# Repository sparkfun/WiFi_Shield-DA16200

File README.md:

SparkFun WiFi Shield DA16200
========================================

[*SparkFun WiFi Shield DA16200 (18567)*](https://www.sparkfun.com/products/18567)

Ultra. Low. Power. Arguably the best three words in the IoT world. SparkFun has teamed up with Dialog to provide you with this [Ultra-Low_Power Wifi Shield](https://www.sparkfun.com/products/18567) based around the DA16200 module. Behold a fully integrated Wi-Fi® module with a 40 MHz crystal oscillator, 32.768 KHz RTC clock, RF Lumped RF filter, 4 M-byte flash memory, and an onboard chip antenna. Add to that a Qwiic connector, MORE STUFF, and you've got pure magic. 

This module is ideal for door locks, thermostats, sensors, pet trackers, asset trackers, sprinkler systems, connected lighting, video cameras, video door bells, wearables and other IoT devices.

The module's certified Wi-Fi alliance for IEEE802.11b/g/n, Wi-Fi Direct, WPS functionalities means it's been approved by multiple countries and using the Wi-Fi Alliance transfer policy, the Wi-Fi Certifications can be transferred without being tested again. 

Repository Contents
-------------------

* **/Hardware** - Eagle design files (.brd, .sch)

Documentation
--------------
* **[Hookup Guide](https://sparkle.sparkfun.com/sparkle/learn_tutorials/1991)** - Basic hookup guide for the SparkFun WiFi Shield DA16200.

License Information
-------------------

This product is _**open source**_! 

Please review the LICENSE.md file for license information. 

If you have any questions or concerns on licensing, please contact technical support on our [SparkFun forums](https://forum.sparkfun.com/viewforum.php?f=152).

Distributed as-is; no warranty is given.

- Your friends at SparkFun.

_<COLLABORATION CREDIT>_

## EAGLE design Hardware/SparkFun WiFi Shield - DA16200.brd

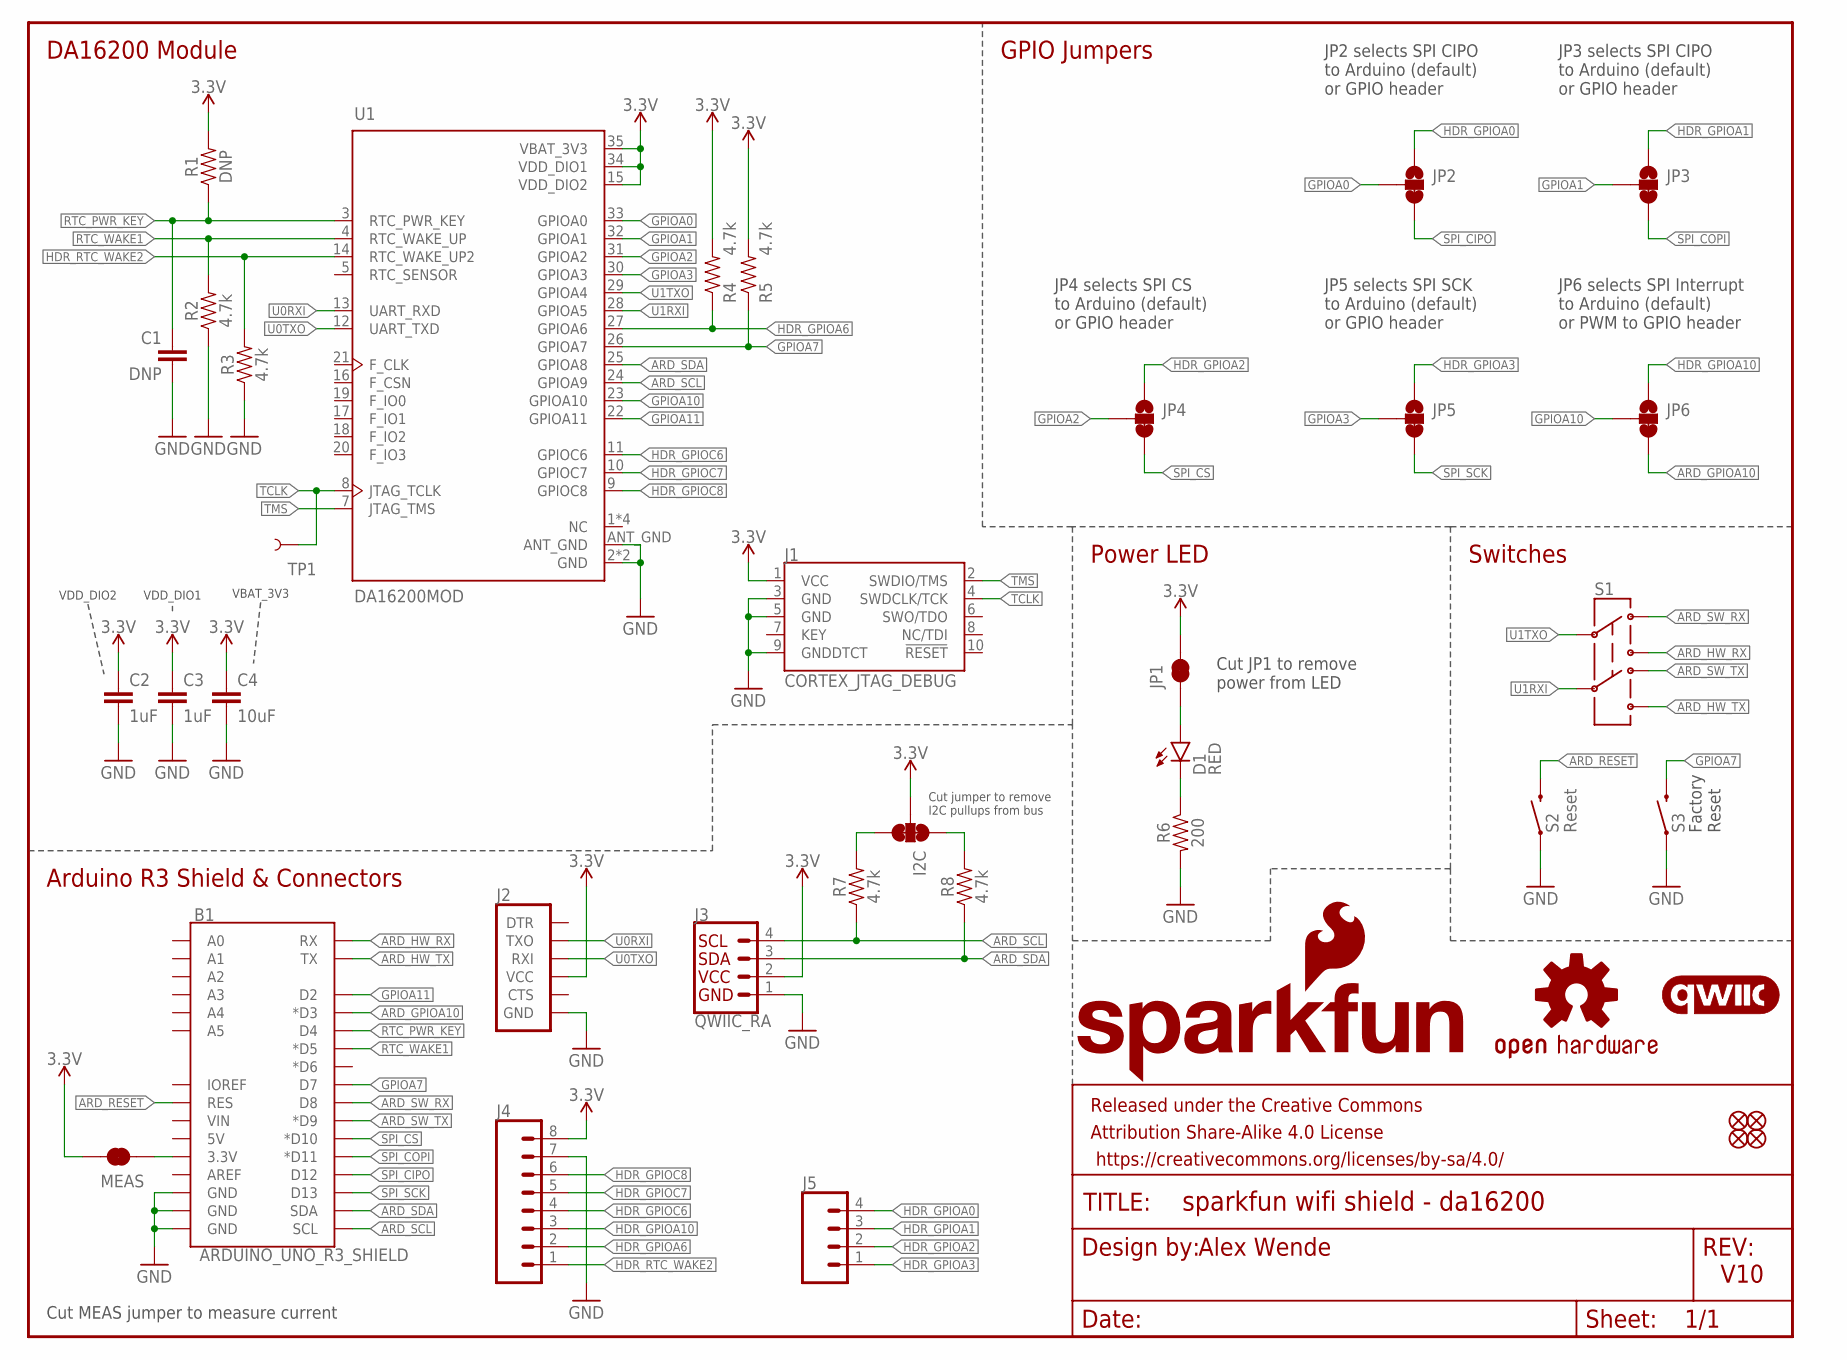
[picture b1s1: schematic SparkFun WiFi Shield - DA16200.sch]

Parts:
B1: ARDUINO_UNO_R3_SHIELD; UNO_R3_SHIELD_NOLABELS_LOCK
C1: DNP; 0603
C2, C3: 1uF; 0603
C4: 10uF; 0603
D1: RED; LED-0603
FD1, FD2, FD3, FD4: FIDUCIAL1X2; FIDUCIAL-1X2
FRAME1: FRAME-LETTER; CREATIVE_COMMONS
I2C: JUMPER-SMT_3_2-NC_TRACE_SILK; SMT-JUMPER_3_2-NC_TRACE_SILK
J1: CORTEX_JTAG_DEBUG; 2X5-PTH-1.27MM-NO_SILK
J2: 6_PIN_SERIAL_TARGET_NO_SILK; 1X06_NO_SILK
J3: QWIIC_RA; JST04_1MM_RA
J4: CONN_08NO_SILK_DNP; 1X08_NO_SILK
J5: CONN_041X04_NO_SILK; 1X04_NO_SILK
JP1: JUMPER-SMT_2_NC_TRACE_SILK; SMT-JUMPER_2_NC_TRACE_SILK
JP2, JP3, JP4, JP5, JP6: JUMPER-SMT_3_1-NC_TRACE_SILK; SMT-JUMPER_3_1-NC_TRACE_SILK
LOGO1: SFE_LOGO_NAME_FLAME.2_INCH; SFE_LOGO_NAME_FLAME_.2
LOGO2: OSHW-LOGOM; OSHW-LOGO-M
LOGO4: QWIIC_LOGO_5MM; QWIIC_5MM
MEAS: JUMPER-COMBO_2_NC_TRACE; COMBO-JUMPER_2_NC_TRACE
R1: DNP; 0603
R2, R3, R4, R5, R7, R8: 4.7k; 0603
R6: 200; 0603
S1: DPDT; SWITCH_DPDT_SMD_AYZ0202
S2: Reset; TACTILE_SWITCH_SMD_5.2MM
S3: MOMENTARY-SWITCH-SPST-SMD-5.2MM-TALL; TACTILE_SWITCH_SMD_5.2MM
TP1: TEST-POINT3; PAD.03X.03
U1: DA16200MOD; XCVR_DA16200MOD-AAC4WA32

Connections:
3.3V: C2.1, C3.1, C4.1, I2C.2, J1.1 (VCC), J2.4 (VCC), J3.2, J4.8, JP1.2, MEAS.1, MEAS.3 (1), R1.2, R4.2, R5.2, U1.15 (VDD_DIO2), U1.34 (VDD_DIO1), U1.35 (VBAT_3V3)
ARD_GPIOA10: B1.D3 (*D3), JP6.3
ARD_HW_RX: B1.RX, S1.1
ARD_HW_TX: B1.TX, S1.4
ARD_RESET: B1.RES, S2.3 (2)
ARD_SCL: B1.SCL, J3.4, R7.1, U1.24 (GPIOA9)
ARD_SDA: B1.SDA, J3.3, R8.1, U1.25 (GPIOA8)
ARD_SW_RX: B1.D8, S1.3
ARD_SW_TX: B1.D9 (*D9), S1.6
GND: B1.GND@0 (GND), B1.GND@1 (GND), B1.GND@2 (GND), C1.2, C2.2, C3.2, C4.2, J1.3 (GND), J1.5 (GND), J1.9 (GNDDTCT), J2.6 (GND), J3.1, J4.7, R2.1, R3.1, R6.2, S2.1, S3.1, U1.2 (GND), U1.ANT_GND, U1.GND
GPIOA0: JP2.2, U1.33 (GPIOA0)
GPIOA1: JP3.2, U1.32 (GPIOA1)
GPIOA2: JP4.2, U1.31 (GPIOA2)
GPIOA3: JP5.2, U1.30 (GPIOA3)
GPIOA7: B1.D7, R5.1, S3.3 (2), U1.26 (GPIOA7)
GPIOA10: JP6.2, U1.23 (GPIOA10)
GPIOA11: B1.D2, U1.22 (GPIOA11)
HDR_GPIOA0: J5.4, JP2.1
HDR_GPIOA1: J5.3, JP3.1
HDR_GPIOA2: J5.2, JP4.1
HDR_GPIOA3: J5.1, JP5.1
HDR_GPIOA6: J4.2, R4.1, U1.27 (GPIOA6)
HDR_GPIOA10: J4.3, JP6.1
HDR_GPIOC6: J4.4, U1.11 (GPIOC6)
HDR_GPIOC7: J4.5, U1.10 (GPIOC7)
HDR_GPIOC8: J4.6, U1.9 (GPIOC8)
HDR_RTC_WAKE2: J4.1, R3.2, U1.14 (RTC_WAKE_UP2)
unnamed: B1.3.3V, MEAS.2, MEAS.4 (2)
unnamed: D1.A, JP1.1
unnamed: I2C.3, R7.2
unnamed: I2C.1, R8.2
unnamed: D1.C, R6.1
RTC_PWR_KEY: B1.D4, C1.1, R1.1, U1.3 (RTC_PWR_KEY)
RTC_WAKE1: B1.D5 (*D5), R2.2, U1.4 (RTC_WAKE_UP)
SPI_CIPO: B1.D12, JP2.3
SPI_COPI: B1.D11 (*D11), JP3.3
SPI_CS: B1.D10 (*D10), JP4.3
SPI_SCK: B1.D13, JP5.3
TCLK: J1.4 (SWDCLK/TCK), TP1.1, U1.8 (JTAG_TCLK)
TMS: J1.2 (SWDIO/TMS), U1.7 (JTAG_TMS)
U0RXI: J2.3 (TXO), U1.13 (UART_RXD)
U0TXO: J2.2 (RXI), U1.12 (UART_TXD)
U1RXI: S1.5, U1.28 (GPIOA5)
U1TXO: S1.2, U1.29 (GPIOA4)

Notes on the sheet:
Factory Reset
DA16200 Module
Arduino R3 Shield & Connectors
Switches
V10
Alex Wende
VDD_DIO2
VDD_DIO1
VBAT_3V3
Power LED
GPIO Jumpers
Cut JP1 to remove power from LED
JP6 selects SPI Interrupt to Arduino (default) or PWM to GPIO header
Cut MEAS jumper to measure current
Cut jumper to remove I2C pullups from bus
JP2 selects SPI CIPO to Arduino (default) or GPIO header
JP3 selects SPI CIPO to Arduino (default) or GPIO header
JP4 selects SPI CS to Arduino (default) or GPIO header
JP5 selects SPI SCK to Arduino (default) or GPIO header

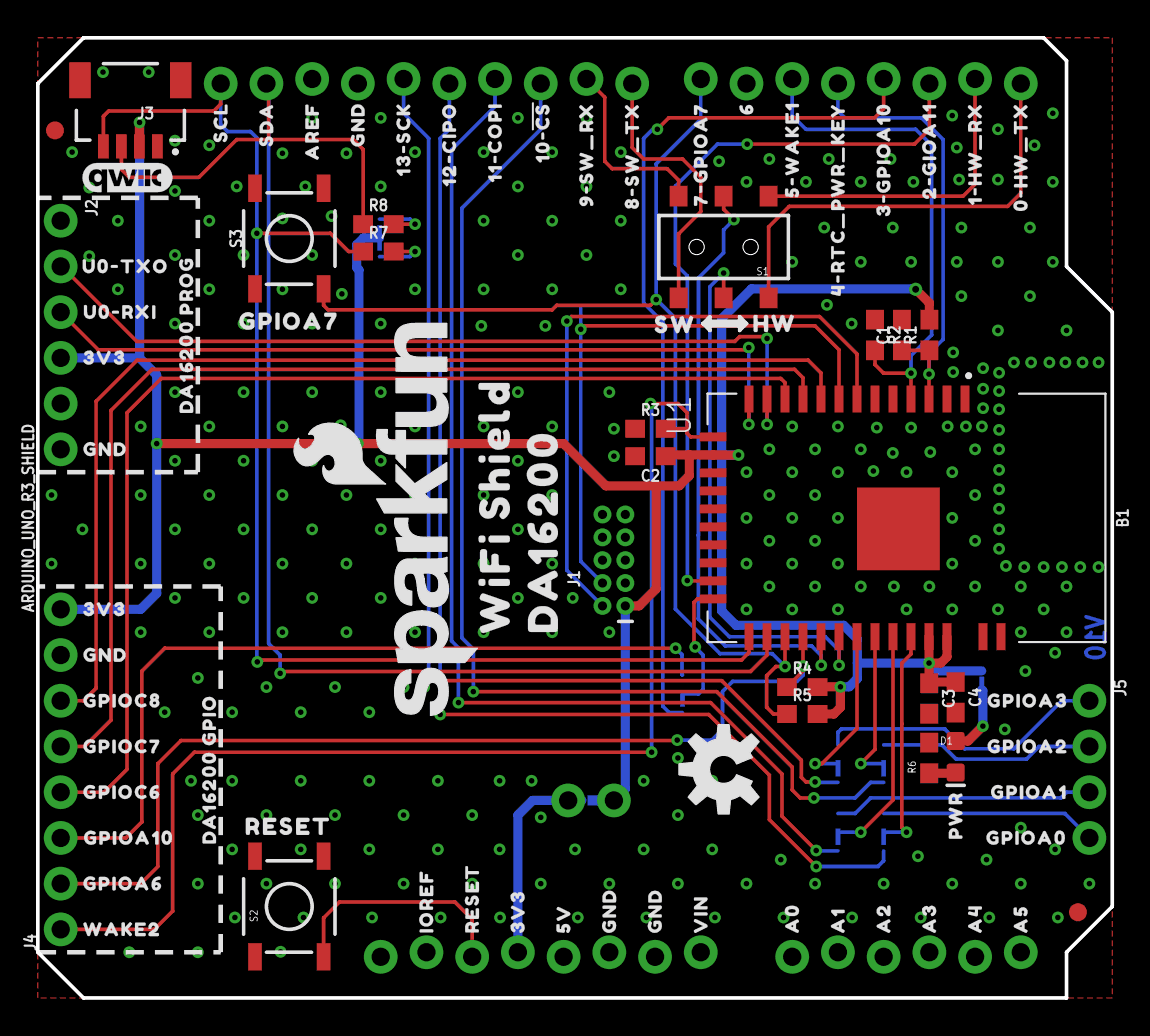
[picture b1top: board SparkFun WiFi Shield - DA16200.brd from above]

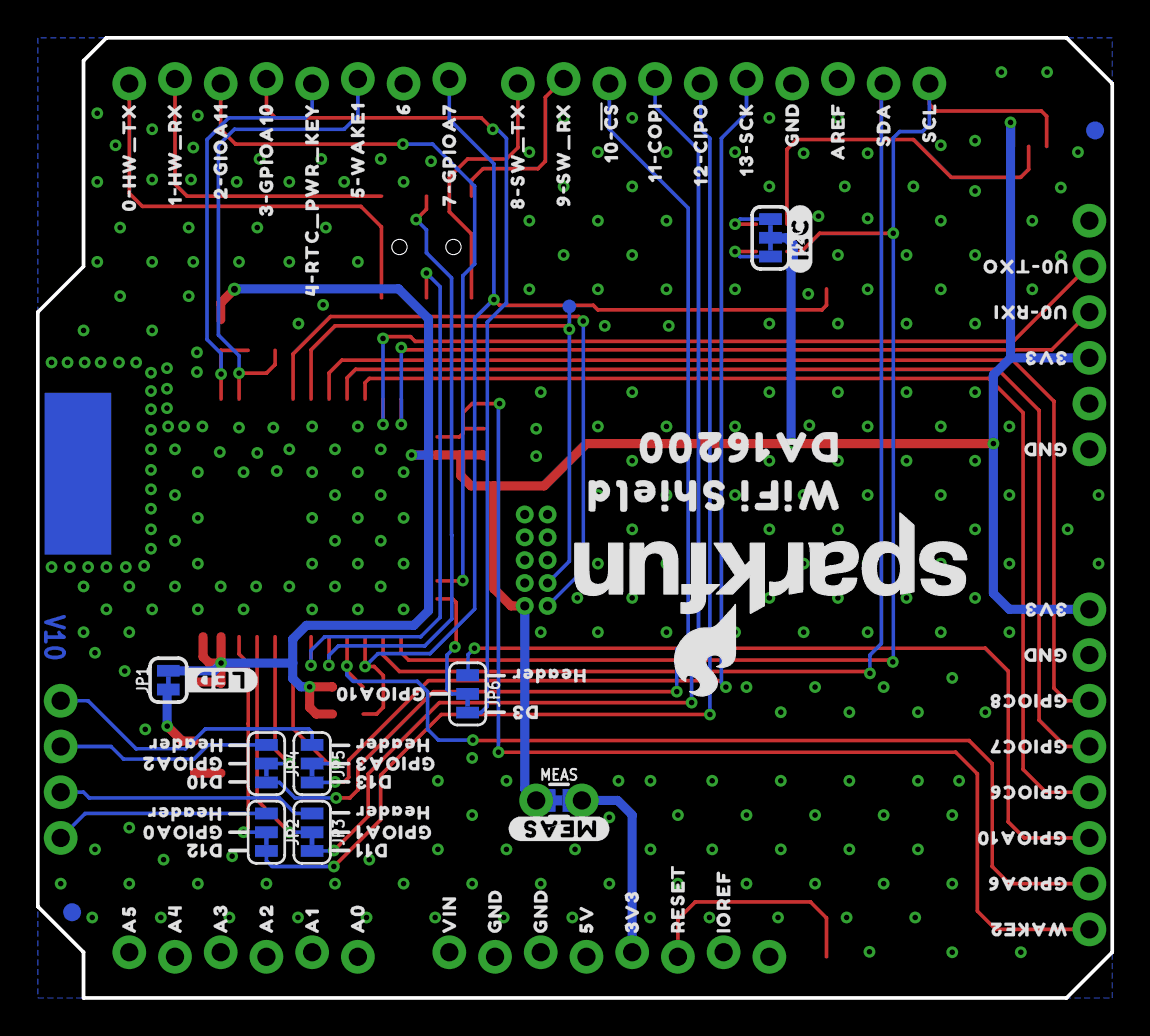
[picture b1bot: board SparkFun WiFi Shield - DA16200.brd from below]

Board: 2 copper layers, 59.7 x 53.3 mm, 160 parts (75 on the bottom side), 44 nets.

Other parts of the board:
LOGO3: SFE_LOGO_NAME_FLAME.2_INCH; SFE_LOGO_NAME_FLAME_.2
U$1, U$16: IOREF0
U$2, U$19: RESET0
U$3, U$37, U$39, U$41, U$85, U$87: 3V30
U$4, U$55: 5V0
U$5, U$6, U$28, U$40, U$52, U$56, U$57, U$79, U$86, U$88: GND0
U$7, U$58: VIN0
U$8, U$59: A00
U$9, U$60: A10
U$10, U$61: A20
U$11, U$62: A30
U$12, U$63: A40
U$13, U$64: A50
U$14, U$65: 0#HW_TX0
U$15, U$66: 1#HW_RX0
U$17, U$95: GPIOA60
U$18, U$70: 4#RTC_PWR_KEY0
U$20, U$73: 8#SW_TX0
U$21, U$72: 7#GPIOA70
U$22, U$67: 2#GIOA110
U$23, U$33: 5#WAKE10
U$24, U$75: 10##CS#0
U$25, U$76: 11#COPI0
U$26, U$77: 12#CIPO0
U$27, U$78: 13#SCK0
U$29, U$80: AREF0
U$30, U$81: SDA0
U$31, U$82: SCL0
U$32, U$74: 9#SW_RX0
U$34: GPIOA70
U$35, U$48: WAKE20
U$36: RESET_0
U$38, U$71: 60
U$42: HW0
U$43: SW0
U$44, U$89: GPIOC80
U$45, U$90: GPIOC70
U$46, U$91: GPIOC60
U$47, U$69, U$92: GPIOA100
U$49: #I2C#0
U$51, U$68: 3#GPIOA100
U$53, U$83: U0#TXO0
U$54, U$84: U0#RXI0
U$93, U$115: GPIOA00
U$94, U$114: GPIOA10
U$96: D30
U$97: #LED#0
U$98: #MEAS#0
U$99: PWR0
U$100, U$107: WIFI_SHIELD0
U$101, U$108: DA162000
U$102, U$116: GPIOA20
U$103, U$117: GPIOA30
U$104: DA16200_GPIO0
U$105: DA16200_PROG0
U$106, U$118, U$119, U$120, U$121: HEADER0
U$122: D100
U$123: D110
U$124: D120
U$125: D130

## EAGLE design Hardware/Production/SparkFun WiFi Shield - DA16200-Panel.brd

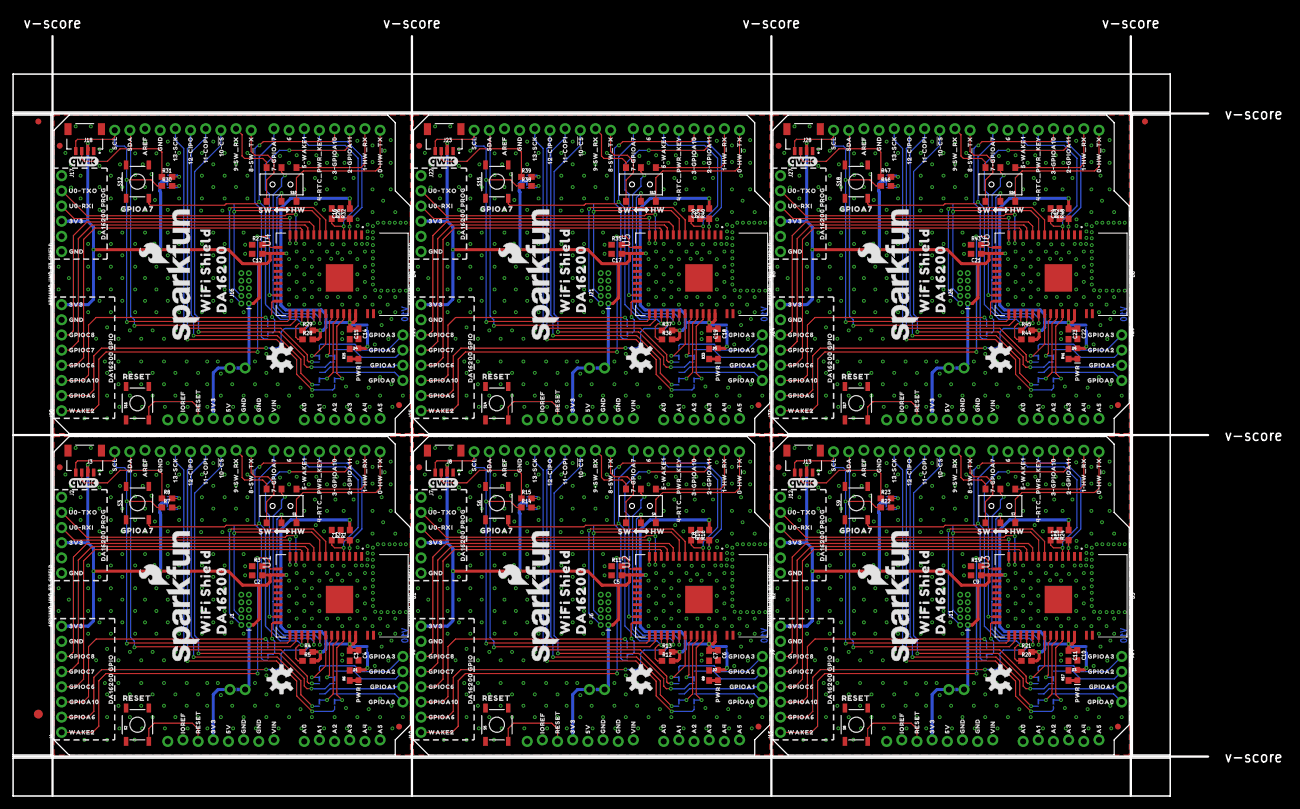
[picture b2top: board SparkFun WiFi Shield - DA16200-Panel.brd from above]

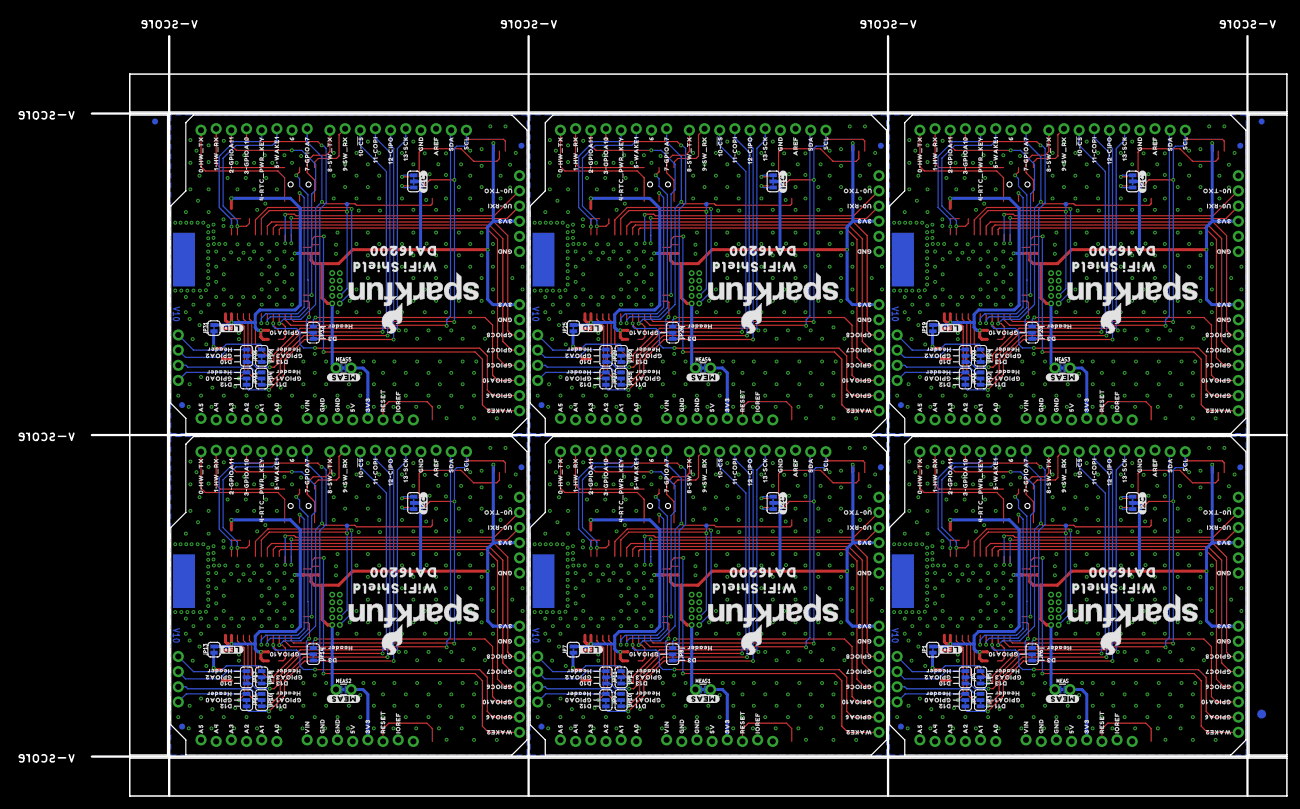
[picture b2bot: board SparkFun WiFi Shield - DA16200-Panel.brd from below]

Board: 2 copper layers, 200.2 x 127.3 mm, 960 parts (453 on the bottom side), 264 nets.

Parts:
B1, B2, B3, B4, B5, B6: ARDUINO_UNO_R3_SHIELD; UNO_R3_SHIELD_NOLABELS_LOCK
C1, C8, C12, C16, C20, C24: DNP; 0603
C2, C3, C5, C7, C9, C11, C13, C15, C17, C19, C21, C23: 1uF; 0603
C4, C6, C10, C14, C18, C22: 10uF; 0603
D1, D2, D3, D4, D5, D6: RED; LED-0603
E$1, E$2, E$3, E$4: FIDUCIAL-1X2
E$5, E$6: FIDUCIAL-1.5X3
FD1, FD2, FD3, FD4, FD5, FD6, FD7, FD8, FD9, FD10, FD11, FD12, FD13, FD14, FD15, FD16, FD17, FD18, FD19, FD20, FD21, FD22, FD23, FD24: FIDUCIAL1X2; FIDUCIAL-1X2
I2C, I2C1, I2C2, I2C3, I2C4, I2C5: SMT-JUMPER_3_2-NC_TRACE_SILK
J1, J6, J11, J16, J21, J26: CORTEX_JTAG_DEBUG; 2X5-PTH-1.27MM-NO_SILK
J2, J7, J12, J17, J22, J27: 1X06_NO_SILK
J3, J8, J13, J18, J23, J28: QWIIC_RA; JST04_1MM_RA
J4, J10, J15, J20, J25, J30: 1X08_NO_SILK
J5, J9, J14, J19, J24, J29: 1X04_NO_SILK
JP1, JP7, JP13, JP19, JP25, JP31: SMT-JUMPER_2_NC_TRACE_SILK
JP2, JP3, JP4, JP5, JP6, JP8, JP9, JP10, JP11, JP12, JP14, JP15, JP16, JP17, JP18, JP20, JP21, JP22, JP23, JP24, JP26, JP27, JP28, JP29, JP30, JP32, JP33, JP34, JP35, JP36: SMT-JUMPER_3_1-NC_TRACE_SILK
LOGO1, LOGO3, LOGO5, LOGO7, LOGO9, LOGO11, LOGO13, LOGO15, LOGO17, LOGO19, LOGO21, LOGO23: SFE_LOGO_NAME_FLAME.2_INCH; SFE_LOGO_NAME_FLAME_.2
LOGO2, LOGO6, LOGO10, LOGO14, LOGO18, LOGO22: OSHW-LOGOM; OSHW-LOGO-M
LOGO4, LOGO8, LOGO12, LOGO16, LOGO20, LOGO24: QWIIC_LOGO_5MM; QWIIC_5MM
MEAS, MEAS1, MEAS2, MEAS3, MEAS4, MEAS5: COMBO-JUMPER_2_NC_TRACE
R1, R16, R24, R32, R40, R48: DNP; 0603
R2, R3, R4, R5, R7, R8, R10, R11, R12, R13, R14, R15, R18, R19, R20, R21, R22, R23, R26, R27, R28, R29, R30, R31, R34, R35, R36, R37, R38, R39, R42, R43, R44, R45, R46, R47: 4.7k; 0603
R6, R9, R17, R25, R33, R41: 200; 0603
S1, S4, S7, S10, S13, S16: DPDT; SWITCH_DPDT_SMD_AYZ0202
S2, S5, S8, S11, S14, S17: Reset; TACTILE_SWITCH_SMD_5.2MM
S3, S6, S9, S12, S15, S18: TACTILE_SWITCH_SMD_5.2MM
TP1, TP2, TP3, TP4, TP5, TP6: PAD.03X.03
U1, U2, U3, U4, U5, U6: DA16200MOD; XCVR_DA16200MOD-AAC4WA32
U$1, U$16, U$22, U$162, U$239, U$281, U$358, U$400, U$477, U$519, U$596, U$638: IOREF0
U$2, U$19, U$67, U$163, U$240, U$282, U$359, U$401, U$478, U$520, U$597, U$639: RESET0
U$3, U$37, U$39, U$41, U$85, U$87, U$110, U$152, U$155, U$164, U$191, U$193, U$241, U$271, U$274, U$283, U$310, U$312, U$360, U$390, U$393, U$402, U$429, U$431, U$479, U$509, U$512, U$521, U$548, U$550, U$598, U$628, U$631, U$640, U$667, U$669: 3V30
U$4, U$55, U$111, U$165, U$242, U$284, U$361, U$403, U$480, U$522, U$599, U$641: 5V0
U$5, U$6, U$28, U$40, U$52, U$56, U$57, U$79, U$86, U$88, U$112, U$113, U$140, U$153, U$154, U$166, U$167, U$185, U$192, U$194, U$243, U$244, U$259, U$272, U$273, U$285, U$286, U$304, U$311, U$313, U$362, U$363, U$378, U$391, U$392, U$404, U$405, U$423, U$430, U$432, U$481, U$482, U$497, U$510, U$511, U$523, U$524, U$542, U$549, U$551, U$600, U$601, U$616, U$629, U$630, U$642, U$643, U$661, U$668, U$670: GND0
U$7, U$58, U$126, U$168, U$245, U$287, U$364, U$406, U$483, U$525, U$602, U$644: VIN0
U$8, U$59, U$127, U$169, U$246, U$288, U$365, U$407, U$484, U$526, U$603, U$645: A00
U$9, U$60, U$128, U$170, U$247, U$289, U$366, U$408, U$485, U$527, U$604, U$646: A10
U$10, U$61, U$129, U$171, U$248, U$290, U$367, U$409, U$486, U$528, U$605, U$647: A20
U$11, U$62, U$130, U$172, U$249, U$291, U$368, U$410, U$487, U$529, U$606, U$648: A30
U$12, U$63, U$131, U$173, U$250, U$292, U$369, U$411, U$488, U$530, U$607, U$649: A40
U$13, U$64, U$132, U$174, U$251, U$293, U$370, U$412, U$489, U$531, U$608, U$650: A50
U$14, U$65, U$133, U$175, U$252, U$294, U$371, U$413, U$490, U$532, U$609, U$651: 0#HW_TX0
U$15, U$66, U$134, U$176, U$253, U$295, U$372, U$414, U$491, U$533, U$610, U$652: 1#HW_RX0
U$17, U$95, U$158, U$199, U$277, U$318, U$396, U$437, U$515, U$556, U$634, U$675: GPIOA60
U$18, U$70, U$231, U$234, U$350, U$353, U$469, U$472, U$588, U$591, U$707, U$710: 4#RTC_PWR_KEY0
U$20, U$73, U$159, U$179, U$278, U$298, U$397, U$417, U$516, U$536, U$635, U$655: 8#SW_TX0
U$21, U$72, U$135, U$178, U$254, U$297, U$373, U$416, U$492, U$535, U$611, U$654: 7#GPIOA70
U$23, U$33, U$232, U$233, U$351, U$352, U$470, U$471, U$589, U$590, U$708, U$709: 5#WAKE10
U$24, U$75, U$136, U$181, U$255, U$300, U$374, U$419, U$493, U$538, U$612, U$657: 10##CS#0
U$25, U$76, U$137, U$182, U$256, U$301, U$375, U$420, U$494, U$539, U$613, U$658: 11#COPI0
U$26, U$77, U$138, U$183, U$257, U$302, U$376, U$421, U$495, U$540, U$614, U$659: 12#CIPO0
U$27, U$78, U$139, U$184, U$258, U$303, U$377, U$422, U$496, U$541, U$615, U$660: 13#SCK0
U$29, U$80, U$141, U$186, U$260, U$305, U$379, U$424, U$498, U$543, U$617, U$662: AREF0
U$30, U$81, U$142, U$187, U$261, U$306, U$380, U$425, U$499, U$544, U$618, U$663: SDA0
U$31, U$82, U$143, U$188, U$262, U$307, U$381, U$426, U$500, U$545, U$619, U$664: SCL0
U$32, U$74, U$160, U$180, U$279, U$299, U$398, U$418, U$517, U$537, U$636, U$656: 9#SW_RX0
U$34, U$144, U$263, U$382, U$501, U$620: GPIOA70
U$35, U$48, U$235, U$236, U$354, U$355, U$473, U$474, U$592, U$593, U$711, U$712: WAKE20
U$36, U$151, U$270, U$389, U$508, U$627: RESET_0
U$38, U$71, U$161, U$177, U$280, U$296, U$399, U$415, U$518, U$534, U$637, U$653: 60
U$42, U$156, U$275, U$394, U$513, U$632: HW0
U$43, U$157, U$276, U$395, U$514, U$633: SW0
U$44, U$89, U$145, U$195, U$264, U$314, U$383, U$433, U$502, U$552, U$621, U$671: GPIOC80
U$45, U$90, U$146, U$196, U$265, U$315, U$384, U$434, U$503, U$553, U$622, U$672: GPIOC70
U$46, U$91, U$147, U$197, U$266, U$316, U$385, U$435, U$504, U$554, U$623, U$673: GPIOC60
U$47, U$69, U$92, U$148, U$198, U$207, U$267, U$317, U$326, U$386, U$436, U$445, U$505, U$555, U$564, U$624, U$674, U$683: GPIOA100
U$49, U$214, U$333, U$452, U$571, U$690: #I2C#0
U$50, U$109, U$237, U$238, U$356, U$357, U$475, U$476, U$594, U$595, U$713, U$714: 2#GPIOA110
U$51, U$68, U$205, U$206, U$324, U$325, U$443, U$444, U$562, U$563, U$681, U$682: 3#GPIOA100
U$53, U$83, U$149, U$189, U$268, U$308, U$387, U$427, U$506, U$546, U$625, U$665: U0#TXO0
U$54, U$84, U$150, U$190, U$269, U$309, U$388, U$428, U$507, U$547, U$626, U$666: U0#RXI0
U$93, U$115, U$216, U$227, U$335, U$346, U$454, U$465, U$573, U$584, U$692, U$703: GPIOA00
U$94, U$114, U$215, U$228, U$334, U$347, U$453, U$466, U$572, U$585, U$691, U$704: GPIOA10
U$96, U$208, U$327, U$446, U$565, U$684: D30
U$97, U$200, U$319, U$438, U$557, U$676: #LED#0
U$98, U$201, U$320, U$439, U$558, U$677: #MEAS#0
U$99, U$202, U$321, U$440, U$559, U$678: PWR0
U$100, U$107, U$210, U$212, U$329, U$331, U$448, U$450, U$567, U$569, U$686, U$688: WIFI_SHIELD0
U$101, U$108, U$211, U$213, U$330, U$332, U$449, U$451, U$568, U$570, U$687, U$689: DA162000
U$102, U$116, U$217, U$229, U$336, U$348, U$455, U$467, U$574, U$586, U$693, U$705: GPIOA20
U$103, U$117, U$218, U$230, U$337, U$349, U$456, U$468, U$575, U$587, U$694, U$706: GPIOA30
U$104, U$203, U$322, U$441, U$560, U$679: DA16200_GPIO0
U$105, U$204, U$323, U$442, U$561, U$680: DA16200_PROG0
U$106, U$118, U$119, U$120, U$121, U$209, U$219, U$220, U$221, U$222, U$328, U$338, U$339, U$340, U$341, U$447, U$457, U$458, U$459, U$460, U$566, U$576, U$577, U$578, U$579, U$685, U$695, U$696, U$697, U$698: HEADER0
U$122, U$223, U$342, U$461, U$580, U$699: D100
U$123, U$224, U$343, U$462, U$581, U$700: D110
U$124, U$225, U$344, U$463, U$582, U$701: D120
U$125, U$226, U$345, U$464, U$583, U$702: D130

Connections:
3.3V: C2.1, C3.1, C4.1, I2C.2, J1.1, J2.4, J3.2, J4.8, JP1.2, MEAS.1, MEAS.3, R1.2, R4.2, R5.2, U1.15, U1.34, U1.35
3.3V1: C5.1, C6.1, C7.1, I2C1.2, J6.1, J7.4, J8.2, J10.8, JP7.2, MEAS1.1, MEAS1.3, R12.2, R13.2, R16.2, U2.15, U2.34, U2.35
3.3V2: C9.1, C10.1, C11.1, I2C2.2, J11.1, J12.4, J13.2, J15.8, JP13.2, MEAS2.1, MEAS2.3, R20.2, R21.2, R24.2, U3.15, U3.34, U3.35
3.3V3: C13.1, C14.1, C15.1, I2C3.2, J16.1, J17.4, J18.2, J20.8, JP19.2, MEAS3.1, MEAS3.3, R28.2, R29.2, R32.2, U4.15, U4.34, U4.35
3.3V4: C17.1, C18.1, C19.1, I2C4.2, J21.1, J22.4, J23.2, J25.8, JP25.2, MEAS4.1, MEAS4.3, R36.2, R37.2, R40.2, U5.15, U5.34, U5.35
3.3V5: C21.1, C22.1, C23.1, I2C5.2, J26.1, J27.4, J28.2, J30.8, JP31.2, MEAS5.1, MEAS5.3, R44.2, R45.2, R48.2, U6.15, U6.34, U6.35
ARD_GPIOA1: B2.D3, JP8.3
ARD_GPIOA2: B3.D3, JP14.3
ARD_GPIOA3: B4.D3, JP20.3
ARD_GPIOA4: B5.D3, JP26.3
ARD_GPIOA5: B6.D3, JP32.3
ARD_GPIOA10: B1.D3, JP6.3
ARD_HW_RX: B1.RX, S1.1
ARD_HW_RX1: B2.RX, S4.1
ARD_HW_RX2: B3.RX, S7.1
ARD_HW_RX3: B4.RX, S10.1
ARD_HW_RX4: B5.RX, S13.1
ARD_HW_RX5: B6.RX, S16.1
ARD_HW_TX: B1.TX, S1.4
ARD_HW_TX1: B2.TX, S4.4
ARD_HW_TX2: B3.TX, S7.4
ARD_HW_TX3: B4.TX, S10.4
ARD_HW_TX4: B5.TX, S13.4
ARD_HW_TX5: B6.TX, S16.4
ARD_RESET: B1.RES, S2.3
ARD_RESET1: B2.RES, S5.3
ARD_RESET2: B3.RES, S8.3
ARD_RESET3: B4.RES, S11.3
ARD_RESET4: B5.RES, S14.3
ARD_RESET5: B6.RES, S17.3
ARD_SCL: B1.SCL, J3.4, R7.1, U1.24
ARD_SCL1: B2.SCL, J8.4, R14.1, U2.24
ARD_SCL2: B3.SCL, J13.4, R22.1, U3.24
ARD_SCL3: B4.SCL, J18.4, R30.1, U4.24
ARD_SCL4: B5.SCL, J23.4, R38.1, U5.24
ARD_SCL5: B6.SCL, J28.4, R46.1, U6.24
ARD_SDA: B1.SDA, J3.3, R8.1, U1.25
ARD_SDA1: B2.SDA, J8.3, R15.1, U2.25
ARD_SDA2: B3.SDA, J13.3, R23.1, U3.25
ARD_SDA3: B4.SDA, J18.3, R31.1, U4.25
ARD_SDA4: B5.SDA, J23.3, R39.1, U5.25
ARD_SDA5: B6.SDA, J28.3, R47.1, U6.25
ARD_SW_RX: B1.D8, S1.3
ARD_SW_RX1: B2.D8, S4.3
ARD_SW_RX2: B3.D8, S7.3
ARD_SW_RX3: B4.D8, S10.3
ARD_SW_RX4: B5.D8, S13.3
ARD_SW_RX5: B6.D8, S16.3
ARD_SW_TX: B1.D9, S1.6
ARD_SW_TX1: B2.D9, S4.6
ARD_SW_TX2: B3.D9, S7.6
ARD_SW_TX3: B4.D9, S10.6
ARD_SW_TX4: B5.D9, S13.6
ARD_SW_TX5: B6.D9, S16.6
GND: B1.GND@0, B1.GND@1, B1.GND@2, C1.2, C2.2, C3.2, C4.2, J1.3, J1.5, J1.9, J2.6, J3.1, J4.7, R2.1, R3.1, R6.2, S2.1, S3.1, U1.2, U1.ANT_GND, U1.GND
GND1: B2.GND@0, B2.GND@1, B2.GND@2, C5.2, C6.2, C7.2, C8.2, J6.3, J6.5, J6.9, J7.6, J8.1, J10.7, R9.2, R10.1, R11.1, S5.1, S6.1, U2.2, U2.ANT_GND, U2.GND
GND2: B3.GND@0, B3.GND@1, B3.GND@2, C9.2, C10.2, C11.2, C12.2, J11.3, J11.5, J11.9, J12.6, J13.1, J15.7, R17.2, R18.1, R19.1, S8.1, S9.1, U3.2, U3.ANT_GND, U3.GND
GND3: B4.GND@0, B4.GND@1, B4.GND@2, C13.2, C14.2, C15.2, C16.2, J16.3, J16.5, J16.9, J17.6, J18.1, J20.7, R25.2, R26.1, R27.1, S11.1, S12.1, U4.2, U4.ANT_GND, U4.GND
GND4: B5.GND@0, B5.GND@1, B5.GND@2, C17.2, C18.2, C19.2, C20.2, J21.3, J21.5, J21.9, J22.6, J23.1, J25.7, R33.2, R34.1, R35.1, S14.1, S15.1, U5.2, U5.ANT_GND, U5.GND
GND5: B6.GND@0, B6.GND@1, B6.GND@2, C21.2, C22.2, C23.2, C24.2, J26.3, J26.5, J26.9, J27.6, J28.1, J30.7, R41.2, R42.1, R43.1, S17.1, S18.1, U6.2, U6.ANT_GND, U6.GND
GPIOA0: JP2.2, U1.33
GPIOA1: JP3.2, U1.32
GPIOA2: JP4.2, U1.31
GPIOA3: JP5.2, U1.30
GPIOA4: B2.D7, R12.1, S6.3, U2.26
GPIOA5: JP8.2, U2.23
GPIOA6: B2.D2, U2.22
GPIOA7: B1.D7, R5.1, S3.3, U1.26
GPIOA8: JP9.2, U2.33
GPIOA9: JP10.2, U2.32
GPIOA10: JP6.2, U1.23
GPIOA11: B1.D2, U1.22
GPIOA12: JP11.2, U2.31
GPIOA13: JP12.2, U2.30
GPIOA14: B3.D7, R20.1, S9.3, U3.26
GPIOA15: JP14.2, U3.23
GPIOA16: B3.D2, U3.22
GPIOA17: JP15.2, U3.33
GPIOA18: JP16.2, U3.32
GPIOA19: JP17.2, U3.31
GPIOA20: JP18.2, U3.30
GPIOA21: B4.D7, R28.1, S12.3, U4.26
GPIOA22: JP20.2, U4.23
GPIOA23: B4.D2, U4.22
GPIOA24: JP21.2, U4.33
GPIOA25: JP22.2, U4.32
GPIOA26: JP23.2, U4.31
GPIOA27: JP24.2, U4.30
GPIOA28: B5.D7, R36.1, S15.3, U5.26
GPIOA29: JP26.2, U5.23
GPIOA30: B5.D2, U5.22
GPIOA31: JP27.2, U5.33
GPIOA32: JP28.2, U5.32
GPIOA33: JP29.2, U5.31
GPIOA34: JP30.2, U5.30
GPIOA35: B6.D7, R44.1, S18.3, U6.26
GPIOA36: JP32.2, U6.23
GPIOA37: B6.D2, U6.22
GPIOA38: JP33.2, U6.33
GPIOA39: JP34.2, U6.32
GPIOA40: JP35.2, U6.31
GPIOA41: JP36.2, U6.30
HDR_GPIOA0: J5.4, JP2.1
HDR_GPIOA1: J5.3, JP3.1
HDR_GPIOA2: J5.2, JP4.1
HDR_GPIOA3: J5.1, JP5.1
HDR_GPIOA4: J9.4, JP9.1
HDR_GPIOA5: J9.3, JP10.1
HDR_GPIOA6: J4.2, R4.1, U1.27
HDR_GPIOA7: J10.3, JP8.1
HDR_GPIOA8: J10.2, R13.1, U2.27
HDR_GPIOA9: J9.2, JP11.1
HDR_GPIOA10: J4.3, JP6.1
HDR_GPIOA11: J9.1, JP12.1
HDR_GPIOA12: J14.4, JP15.1
HDR_GPIOA13: J14.3, JP16.1
HDR_GPIOA14: J15.3, JP14.1
HDR_GPIOA15: J15.2, R21.1, U3.27
HDR_GPIOA16: J14.2, JP17.1
HDR_GPIOA17: J14.1, JP18.1
HDR_GPIOA18: J19.4, JP21.1
HDR_GPIOA19: J19.3, JP22.1
HDR_GPIOA20: J20.3, JP20.1
HDR_GPIOA21: J20.2, R29.1, U4.27
HDR_GPIOA22: J19.2, JP23.1
HDR_GPIOA23: J19.1, JP24.1
HDR_GPIOA24: J24.4, JP27.1
HDR_GPIOA25: J24.3, JP28.1
HDR_GPIOA26: J25.3, JP26.1
HDR_GPIOA27: J25.2, R37.1, U5.27
HDR_GPIOA28: J24.2, JP29.1
HDR_GPIOA29: J24.1, JP30.1
HDR_GPIOA30: J29.4, JP33.1
HDR_GPIOA31: J29.3, JP34.1
HDR_GPIOA32: J30.3, JP32.1
HDR_GPIOA33: J30.2, R45.1, U6.27
HDR_GPIOA34: J29.2, JP35.1
HDR_GPIOA35: J29.1, JP36.1
HDR_GPIOC1: J10.4, U2.11
HDR_GPIOC2: J10.5, U2.10
HDR_GPIOC3: J10.6, U2.9
HDR_GPIOC4: J15.4, U3.11
HDR_GPIOC5: J15.5, U3.10
HDR_GPIOC6: J4.4, U1.11
HDR_GPIOC7: J4.5, U1.10
HDR_GPIOC8: J4.6, U1.9
HDR_GPIOC9: J15.6, U3.9
HDR_GPIOC10: J20.4, U4.11
HDR_GPIOC11: J20.5, U4.10
HDR_GPIOC12: J20.6, U4.9
HDR_GPIOC13: J25.4, U5.11
HDR_GPIOC14: J25.5, U5.10
HDR_GPIOC15: J25.6, U5.9
HDR_GPIOC16: J30.4, U6.11
HDR_GPIOC17: J30.5, U6.10
HDR_GPIOC18: J30.6, U6.9
HDR_RTC_WAKE1: J10.1, R11.2, U2.14
HDR_RTC_WAKE2: J4.1, R3.2, U1.14
HDR_RTC_WAKE3: J15.1, R19.2, U3.14
HDR_RTC_WAKE4: J20.1, R27.2, U4.14
HDR_RTC_WAKE5: J25.1, R35.2, U5.14
HDR_RTC_WAKE6: J30.1, R43.2, U6.14
unnamed: B1.3.3V, MEAS.2, MEAS.4
unnamed: D1.A, JP1.1
unnamed: I2C.3, R7.2
unnamed: I2C.1, R8.2
unnamed: D1.C, R6.1
unnamed: D2.C, R9.1
unnamed: B2.3.3V, MEAS1.2, MEAS1.4
unnamed: D2.A, JP7.1
unnamed: I2C1.3, R14.2
unnamed: I2C1.1, R15.2
unnamed: D3.C, R17.1
unnamed: B3.3.3V, MEAS2.2, MEAS2.4
unnamed: D3.A, JP13.1
unnamed: I2C2.3, R22.2
unnamed: I2C2.1, R23.2
unnamed: D4.C, R25.1
unnamed: B4.3.3V, MEAS3.2, MEAS3.4
unnamed: D4.A, JP19.1
unnamed: I2C3.3, R30.2
unnamed: I2C3.1, R31.2
unnamed: D5.C, R33.1
unnamed: B5.3.3V, MEAS4.2, MEAS4.4
unnamed: D5.A, JP25.1
unnamed: I2C4.3, R38.2
unnamed: I2C4.1, R39.2
unnamed: D6.C, R41.1
unnamed: B6.3.3V, MEAS5.2, MEAS5.4
unnamed: D6.A, JP31.1
unnamed: I2C5.3, R46.2
unnamed: I2C5.1, R47.2
RTC_PWR_KEY: B1.D4, C1.1, R1.1, U1.3
RTC_PWR_KEY1: B2.D4, C8.1, R16.1, U2.3
RTC_PWR_KEY2: B3.D4, C12.1, R24.1, U3.3
RTC_PWR_KEY3: B4.D4, C16.1, R32.1, U4.3
RTC_PWR_KEY4: B5.D4, C20.1, R40.1, U5.3
RTC_PWR_KEY5: B6.D4, C24.1, R48.1, U6.3
RTC_WAKE1: B1.D5, R2.2, U1.4
RTC_WAKE2: B2.D5, R10.2, U2.4
RTC_WAKE3: B3.D5, R18.2, U3.4
RTC_WAKE4: B4.D5, R26.2, U4.4
RTC_WAKE5: B5.D5, R34.2, U5.4
RTC_WAKE6: B6.D5, R42.2, U6.4
SPI_CIPO: B1.D12, JP2.3
SPI_CIPO1: B2.D12, JP9.3
SPI_CIPO2: B3.D12, JP15.3
SPI_CIPO3: B4.D12, JP21.3
SPI_CIPO4: B5.D12, JP27.3
SPI_CIPO5: B6.D12, JP33.3
SPI_COPI: B1.D11, JP3.3
SPI_COPI1: B2.D11, JP10.3
SPI_COPI2: B3.D11, JP16.3
SPI_COPI3: B4.D11, JP22.3
SPI_COPI4: B5.D11, JP28.3
SPI_COPI5: B6.D11, JP34.3
SPI_CS: B1.D10, JP4.3
SPI_CS1: B2.D10, JP11.3
SPI_CS2: B3.D10, JP17.3
SPI_CS3: B4.D10, JP23.3
SPI_CS4: B5.D10, JP29.3
SPI_CS5: B6.D10, JP35.3
SPI_SCK: B1.D13, JP5.3
SPI_SCK1: B2.D13, JP12.3
SPI_SCK2: B3.D13, JP18.3
SPI_SCK3: B4.D13, JP24.3
SPI_SCK4: B5.D13, JP30.3
SPI_SCK5: B6.D13, JP36.3
TCLK: J1.4, TP1.1, U1.8
TCLK1: J6.4, TP2.1, U2.8
TCLK2: J11.4, TP3.1, U3.8
TCLK3: J16.4, TP4.1, U4.8
TCLK4: J21.4, TP5.1, U5.8
TCLK5: J26.4, TP6.1, U6.8
TMS: J1.2, U1.7
TMS1: J6.2, U2.7
TMS2: J11.2, U3.7
TMS3: J16.2, U4.7
TMS4: J21.2, U5.7
TMS5: J26.2, U6.7
U0RXI: J2.3, U1.13
U0RXI1: J7.3, U2.13
U0RXI2: J12.3, U3.13
U0RXI3: J17.3, U4.13
U0RXI4: J22.3, U5.13
U0RXI5: J27.3, U6.13
U0TXO: J2.2, U1.12
U0TXO1: J7.2, U2.12
U0TXO2: J12.2, U3.12
U0TXO3: J17.2, U4.12
U0TXO4: J22.2, U5.12
U0TXO5: J27.2, U6.12
U1RXI: S1.5, U1.28
U1RXI1: S4.5, U2.28
U1RXI2: S7.5, U3.28
U1RXI3: S10.5, U4.28
U1RXI4: S13.5, U5.28
U1RXI5: S16.5, U6.28
U1TXO: S1.2, U1.29
U1TXO1: S4.2, U2.29
U1TXO2: S7.2, U3.29
U1TXO3: S10.2, U4.29
U1TXO4: S13.2, U5.29
U1TXO5: S16.2, U6.29

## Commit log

2021-07-26 V10 Dialog Changes
    - GPIOA6 needs 4.7k Pullup
    - GPIOA10 - added 2-way jumper for MCU (SPI Interrupt) and Header (PWM)
    - GPIOC6,7,8 not needed for JTAG
    - Removed RTC Sensor, RTC_WAKE1, RTC_WAKE2
    - PCB - Moved VDD trace, enlarged ground connection for RF GND on bottom, added more vias in large ground areas
2021-07-26 Parts Update
    Updated library for module, added 470k resistor, updated symbols, added jumper notes
2021-07-27 Added I2C
    Added I2C connections, Qwiic connector, pullup resistors, and jumper
2021-07-27 V10 Design Review Changes
    Updated label positions, added notes to sch
2021-07-28 Final Feedback Changes
    Changed R3 footprint to locking
    Added DNP Capacitor and Resistor
2021-07-29 Added jumpers for GPIOA0-3
    Jumpers select between either SPI or GPIO/ADC functionality on the DA16200
2021-07-30 Update SparkFun WiFi Shield - DA16200.brd
    Updated vias
2021-08-03 Added Gerbers
2021-08-05 Panel update
    Moved fiducials away from v-score
2021-08-10 Update SparkFun WiFi Shield - DA16200.sch
    Fixed typo for JP3

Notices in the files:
parts and their libraries:
SparkFun-Boards: Licensing: Creative Commons ShareAlike 4.0 International - https://creativecommons.org/licenses/by-sa/4.0
SparkFun-Aesthetics: Released under the Creative Commons Attribution Share-Alike 4.0 License
SparkFun-Aesthetics: https://creativecommons.org/licenses/by-sa/4.0
